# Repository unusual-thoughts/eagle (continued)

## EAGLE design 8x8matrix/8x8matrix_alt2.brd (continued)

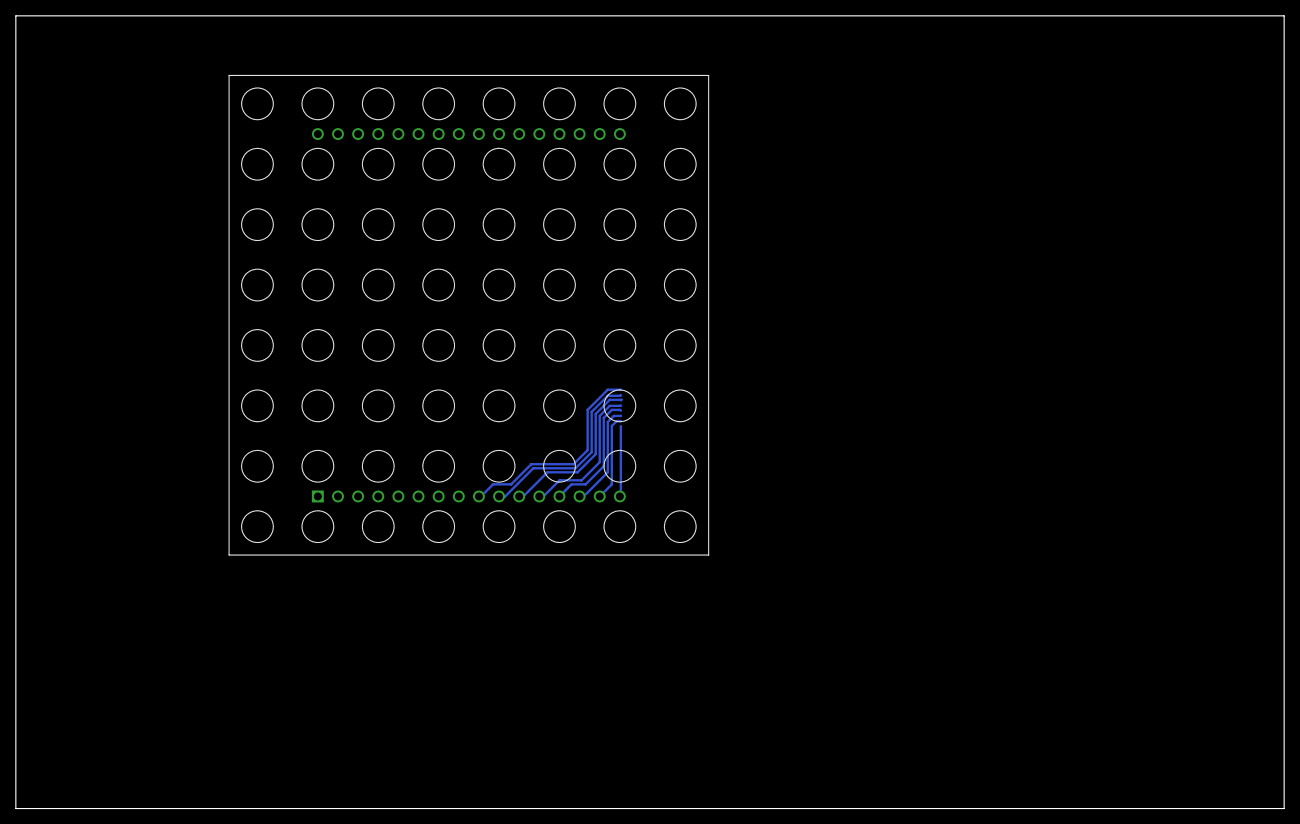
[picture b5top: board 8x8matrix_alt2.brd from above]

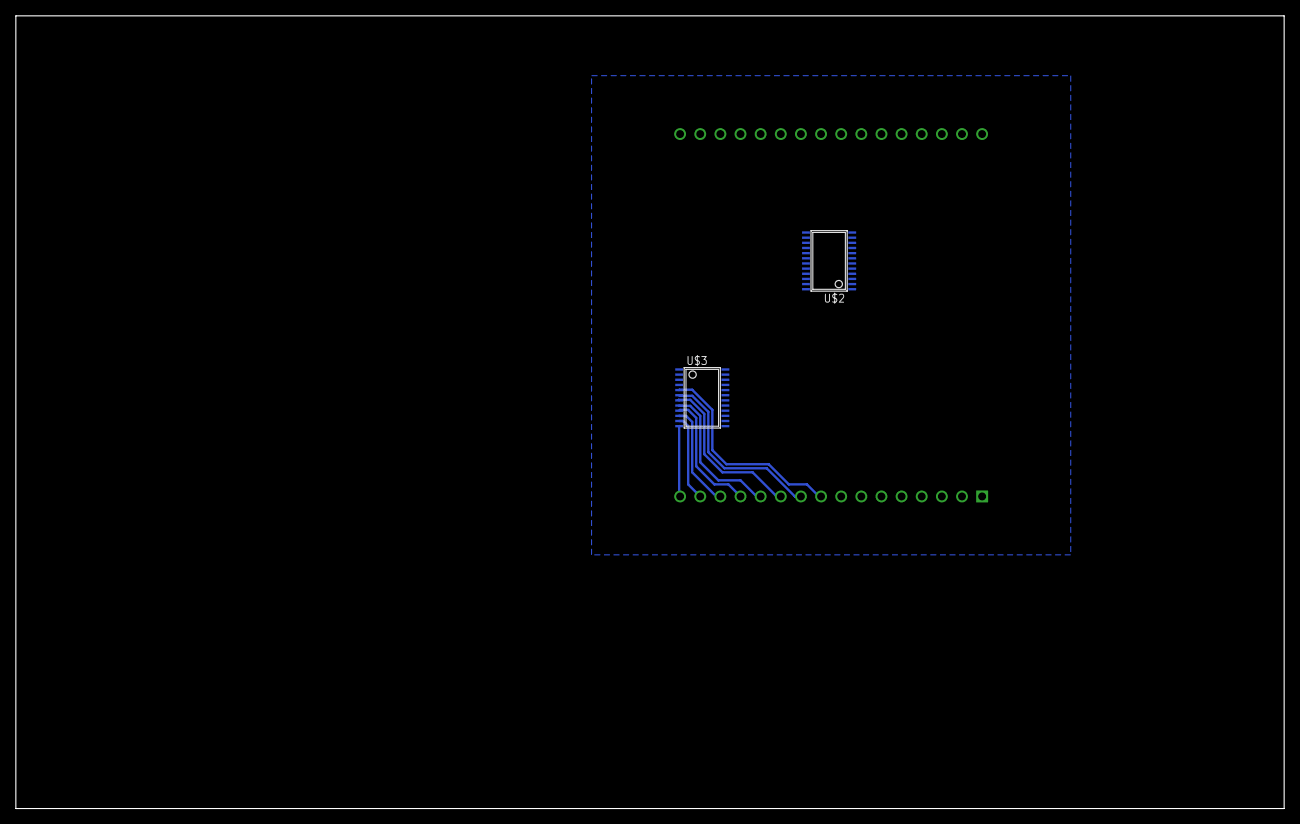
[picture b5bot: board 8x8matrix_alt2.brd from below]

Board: 2 copper layers, 160.0 x 100.0 mm, 3 parts (2 on the bottom side), 21 nets.

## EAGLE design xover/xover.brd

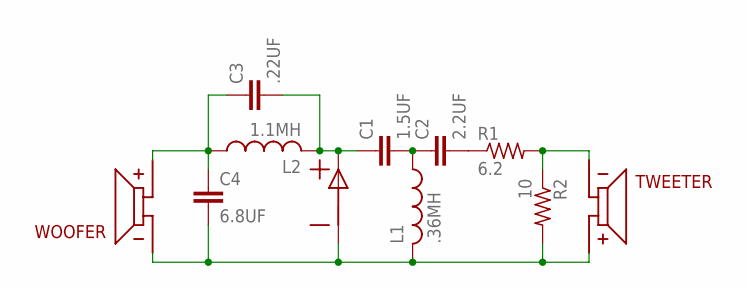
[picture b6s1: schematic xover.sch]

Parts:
C1: 1.5UF
C2: 2.2UF
C3: .22UF
C4: 6.8UF
INPUT: INPUTREV; SCREW
L1: .36MH; .36VERT
L2: 1.1MH
R1: 6.2
R2: 10; 6.2
TWEETER: TWEETER; SCREW
WOOFER: TWEETER; SCREW

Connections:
unnamed: C1.P$1 (1), C3.P$2 (2), INPUT.P$1 (PLUS), L2.P$1 (2)
unnamed: C2.P$2 (2), R1.P$1 (1)
unnamed: C3.P$1 (1), C4.P$1 (1), L2.P$2 (1), WOOFER.P$2 (PLUS)
unnamed: R1.P$2 (2), R2.P$1 (1), TWEETER.P$1 (MINUS)
unnamed: C4.P$2 (2), INPUT.P$2 (MINUS), L1.P$1 (2), R2.P$2 (2), TWEETER.P$2 (PLUS), WOOFER.P$1 (MINUS)
unnamed: C1.P$2 (2), C2.P$1 (1), L1.P$2 (1)

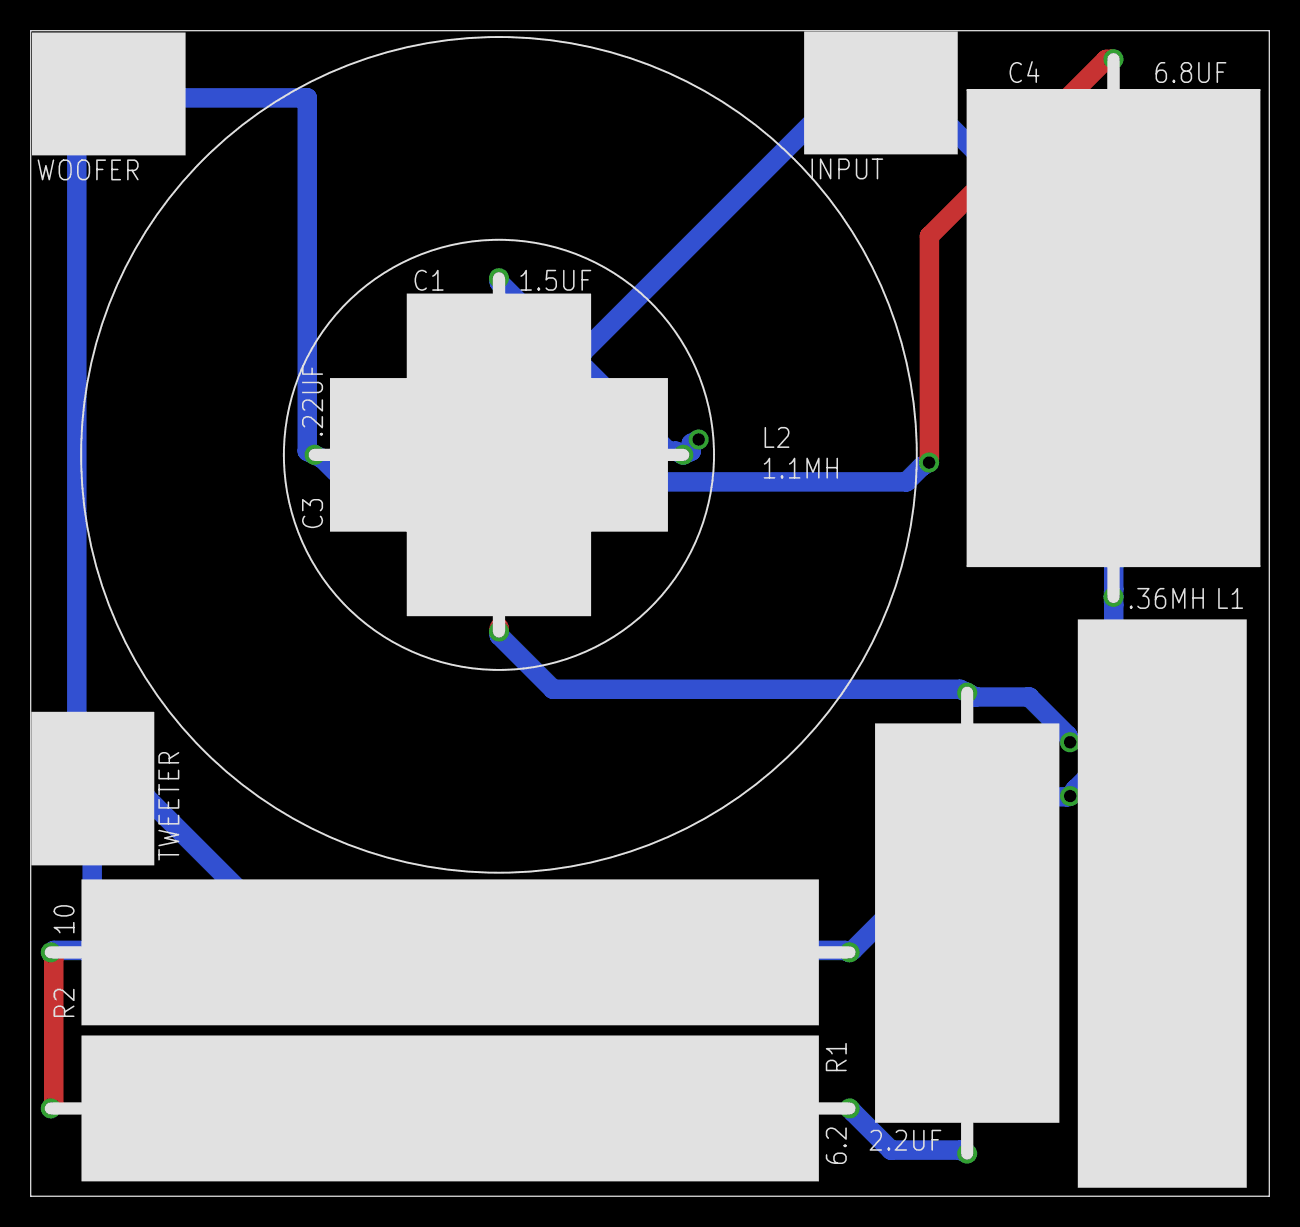
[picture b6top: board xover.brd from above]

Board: 2 copper layers, 80.6 x 75.9 mm, 11 parts (0 on the bottom side), 6 nets.

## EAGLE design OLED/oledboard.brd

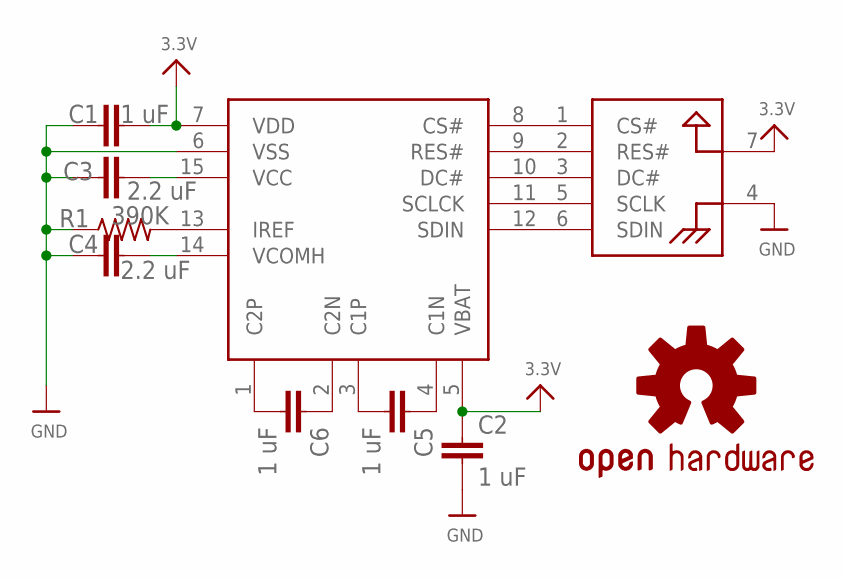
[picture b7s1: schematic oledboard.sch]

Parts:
C1, C2, C5, C6: 1 uF; C0805
C3, C4: 2.2 uF; C0805
LOGO1: OSHW.SYMS; OSHW-LOGO-S
R1: 390K; R0805
U$1: UG-2832HSWEG04
U$6: CONNECTOR

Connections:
3.3V: C1.2, C2.1, U$1.5 (VBAT), U$1.7 (VDD), U$6.7 (GND)
CS: U$1.8 (CS#), U$6.1 (CS#)
DC: U$1.10 (DC#), U$6.3 (DC#)
GND: C1.1, C2.2, C3.1, C4.1, R1.1, U$1.6 (VSS), U$6.4 (3.3V)
unnamed: C5.1, U$1.4 (C1N)
unnamed: C5.2, U$1.3 (C1P)
unnamed: C6.1, U$1.2 (C2N)
unnamed: C6.2, U$1.1 (C2P)
unnamed: R1.2, U$1.13 (IREF)
RES: U$1.9 (RES#), U$6.2 (RES#)
SCLK: U$1.11 (SCLCK), U$6.5 (SCLK)
SDIN: U$1.12 (SDIN), U$6.6 (SDIN)
VCC: C3.2, U$1.15 (VCC)
VCOMH: C4.2, U$1.14 (VCOMH)

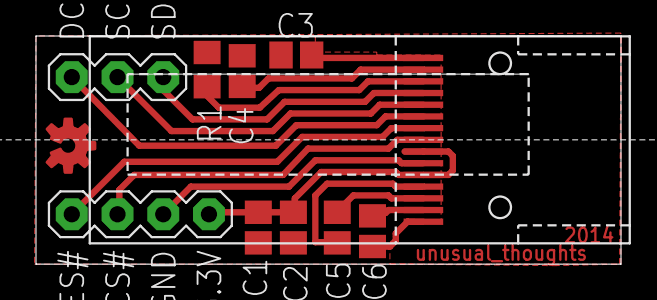
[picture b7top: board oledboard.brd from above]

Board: 2 copper layers, 32.5 x 12.7 mm, 10 parts (0 on the bottom side), 14 nets.

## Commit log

2014-08-07 merge from dropbox
    added my eagle folder from dropbox
2014-08-07 add eagle gitignore
2014-08-07 remove gitignored files
2014-08-07 remove gitignored files lbr
2014-08-08 resistor to smd and add 3.3v
2014-08-08 cosmetic
2014-08-15 working 8x8 matrix board (tlc4)
2014-09-01 added and changed soldermask
2014-09-02 added 4mil and 10mil versions of soldermask
2014-09-02 merged soldermask into one pdf
2014-09-03 fixed gitignore
2014-09-03 flipped so ink is on the right side
2014-09-05 made traces thicker
2014-09-10 corrected bug where ground continuity was broken
2014-09-10 eagle 7
2014-09-20 tlc2
2014-09-20 tlc3
2014-09-20 tried adding FZTA92 darlingtons
2014-09-20 tried with regular SOT23 PNPs
2014-09-20 tried with BCR198S pnp arrays
2014-09-20 found something that works: IRF7104
2014-09-20 removed old file
2014-09-20 renamed pdf
2014-09-20 updated pdf
2014-09-20 enamed soldermask
2014-09-20 changed 238 to 138
2014-09-20 updated soldermask
2014-09-20 cloned pdf
2014-09-20 dropbox fuckup
2014-09-22 changed trace width to 15mil
2014-09-22 cleaned up space beteween traces
2014-09-22 removed autoroute stuff
2014-09-23 reprint
2014-09-23 pdf gen
2014-09-25 soldermask
2014-09-30 added prints
2014-09-30 moved to separate folder
2014-09-30 added matrix readme
